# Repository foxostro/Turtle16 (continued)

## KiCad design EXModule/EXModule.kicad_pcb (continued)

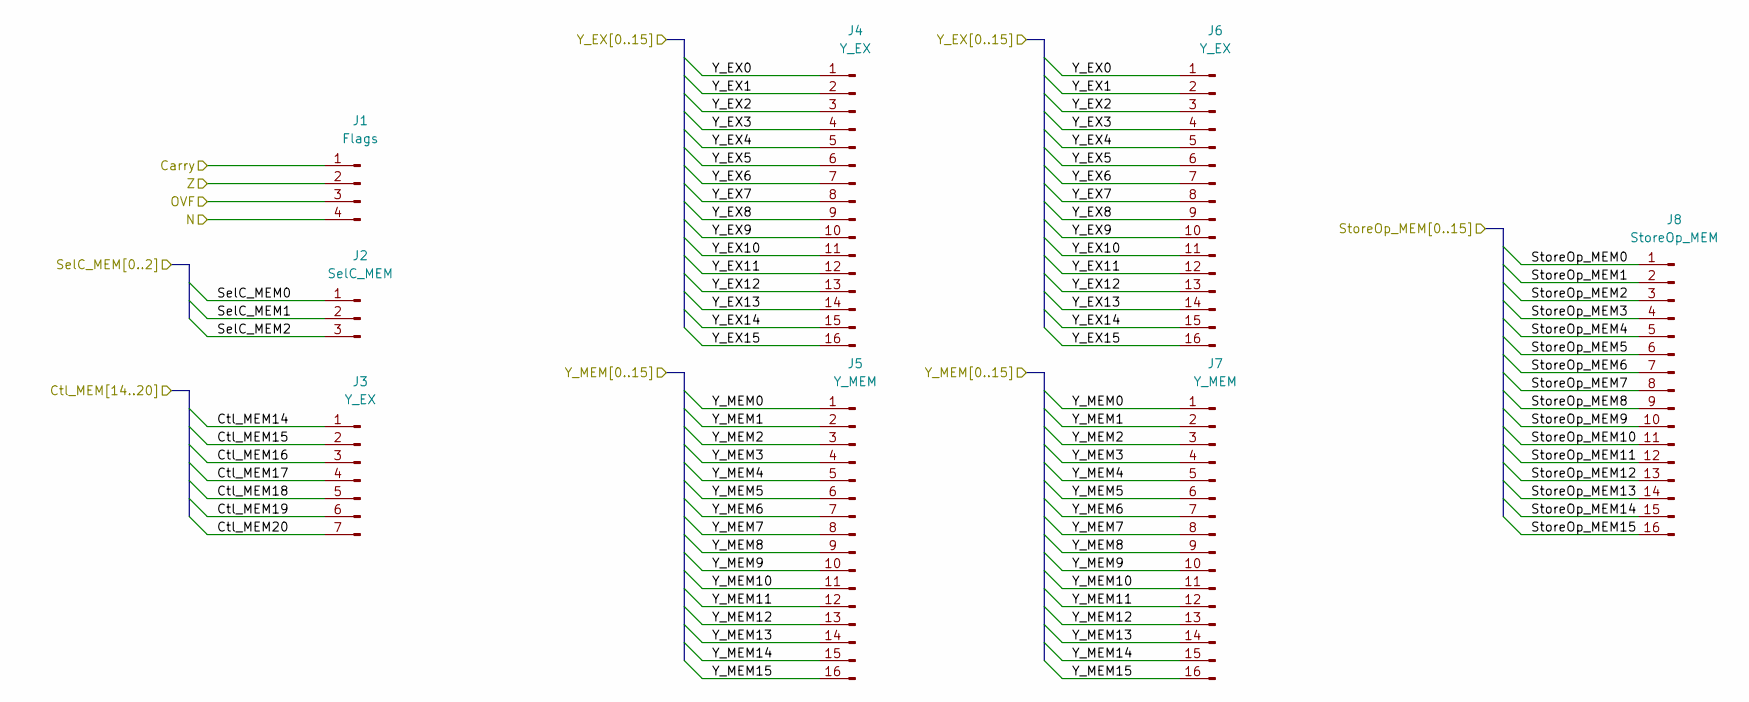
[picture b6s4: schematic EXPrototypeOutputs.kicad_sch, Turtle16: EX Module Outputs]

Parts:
J1: Flags; PinHeader_1x04_P2.54mm_Vertical
J2: SelC_MEM; PinHeader_1x03_P2.54mm_Vertical
J3: Y_EX; PinHeader_1x07_P2.54mm_Vertical
J4, J6: Y_EX; PinHeader_1x16_P2.54mm_Vertical
J5, J7: Y_MEM; PinHeader_1x16_P2.54mm_Vertical
J8: StoreOp_MEM; PinHeader_1x16_P2.54mm_Vertical

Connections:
/EX Prototype Outputs/Carry: J1.1; also elsewhere on the board
/EX Prototype Outputs/Ctl_MEM14: J3.1; also elsewhere on the board
/EX Prototype Outputs/Ctl_MEM15: J3.2; also elsewhere on the board
/EX Prototype Outputs/Ctl_MEM16: J3.3; also elsewhere on the board
/EX Prototype Outputs/Ctl_MEM17: J3.4; also elsewhere on the board
/EX Prototype Outputs/Ctl_MEM18: J3.5; also elsewhere on the board
/EX Prototype Outputs/Ctl_MEM19: J3.6; also elsewhere on the board
/EX Prototype Outputs/Ctl_MEM20: J3.7; also elsewhere on the board
/EX Prototype Outputs/N: J1.4; also elsewhere on the board
/EX Prototype Outputs/OVF: J1.3; also elsewhere on the board
/EX Prototype Outputs/SelC_MEM0: J2.1; also elsewhere on the board
/EX Prototype Outputs/SelC_MEM1: J2.2; also elsewhere on the board
/EX Prototype Outputs/SelC_MEM2: J2.3; also elsewhere on the board
/EX Prototype Outputs/StoreOp_MEM0: J8.1; also elsewhere on the board
/EX Prototype Outputs/StoreOp_MEM1: J8.2; also elsewhere on the board
/EX Prototype Outputs/StoreOp_MEM2: J8.3; also elsewhere on the board
/EX Prototype Outputs/StoreOp_MEM3: J8.4; also elsewhere on the board
/EX Prototype Outputs/StoreOp_MEM4: J8.5; also elsewhere on the board
/EX Prototype Outputs/StoreOp_MEM5: J8.6; also elsewhere on the board
/EX Prototype Outputs/StoreOp_MEM6: J8.7; also elsewhere on the board
/EX Prototype Outputs/StoreOp_MEM7: J8.8; also elsewhere on the board
/EX Prototype Outputs/StoreOp_MEM8: J8.9; also elsewhere on the board
/EX Prototype Outputs/StoreOp_MEM9: J8.10; also elsewhere on the board
/EX Prototype Outputs/StoreOp_MEM10: J8.11; also elsewhere on the board
/EX Prototype Outputs/StoreOp_MEM11: J8.12; also elsewhere on the board
/EX Prototype Outputs/StoreOp_MEM12: J8.13; also elsewhere on the board
/EX Prototype Outputs/StoreOp_MEM13: J8.14; also elsewhere on the board
/EX Prototype Outputs/StoreOp_MEM14: J8.15; also elsewhere on the board
/EX Prototype Outputs/StoreOp_MEM15: J8.16; also elsewhere on the board
/EX Prototype Outputs/Y_EX0: J4.1, J6.1; also elsewhere on the board
/EX Prototype Outputs/Y_EX1: J4.2, J6.2; also elsewhere on the board
/EX Prototype Outputs/Y_EX2: J4.3, J6.3; also elsewhere on the board
/EX Prototype Outputs/Y_EX3: J4.4, J6.4; also elsewhere on the board
/EX Prototype Outputs/Y_EX4: J4.5, J6.5; also elsewhere on the board
/EX Prototype Outputs/Y_EX5: J4.6, J6.6; also elsewhere on the board
/EX Prototype Outputs/Y_EX6: J4.7, J6.7; also elsewhere on the board
/EX Prototype Outputs/Y_EX7: J4.8, J6.8; also elsewhere on the board
/EX Prototype Outputs/Y_EX8: J4.9, J6.9; also elsewhere on the board
/EX Prototype Outputs/Y_EX9: J4.10, J6.10; also elsewhere on the board
/EX Prototype Outputs/Y_EX10: J4.11, J6.11; also elsewhere on the board
/EX Prototype Outputs/Y_EX11: J4.12, J6.12; also elsewhere on the board
/EX Prototype Outputs/Y_EX12: J4.13, J6.13; also elsewhere on the board
/EX Prototype Outputs/Y_EX13: J4.14, J6.14; also elsewhere on the board
/EX Prototype Outputs/Y_EX14: J4.15, J6.15; also elsewhere on the board
/EX Prototype Outputs/Y_EX15: J4.16, J6.16; also elsewhere on the board
/EX Prototype Outputs/Y_MEM0: J5.1, J7.1; also elsewhere on the board
/EX Prototype Outputs/Y_MEM1: J5.2, J7.2; also elsewhere on the board
/EX Prototype Outputs/Y_MEM2: J5.3, J7.3; also elsewhere on the board
/EX Prototype Outputs/Y_MEM3: J5.4, J7.4; also elsewhere on the board
/EX Prototype Outputs/Y_MEM4: J5.5, J7.5; also elsewhere on the board
/EX Prototype Outputs/Y_MEM5: J5.6, J7.6; also elsewhere on the board
/EX Prototype Outputs/Y_MEM6: J5.7, J7.7; also elsewhere on the board
/EX Prototype Outputs/Y_MEM7: J5.8, J7.8; also elsewhere on the board
/EX Prototype Outputs/Y_MEM8: J5.9, J7.9; also elsewhere on the board
/EX Prototype Outputs/Y_MEM9: J5.10, J7.10; also elsewhere on the board
/EX Prototype Outputs/Y_MEM10: J5.11, J7.11; also elsewhere on the board
/EX Prototype Outputs/Y_MEM11: J5.12, J7.12; also elsewhere on the board
/EX Prototype Outputs/Y_MEM12: J5.13, J7.13; also elsewhere on the board
/EX Prototype Outputs/Y_MEM13: J5.14, J7.14; also elsewhere on the board
/EX Prototype Outputs/Y_MEM14: J5.15, J7.15; also elsewhere on the board
/EX Prototype Outputs/Y_MEM15: J5.16, J7.16; also elsewhere on the board
/EX Prototype Outputs/Z: J1.2; also elsewhere on the board

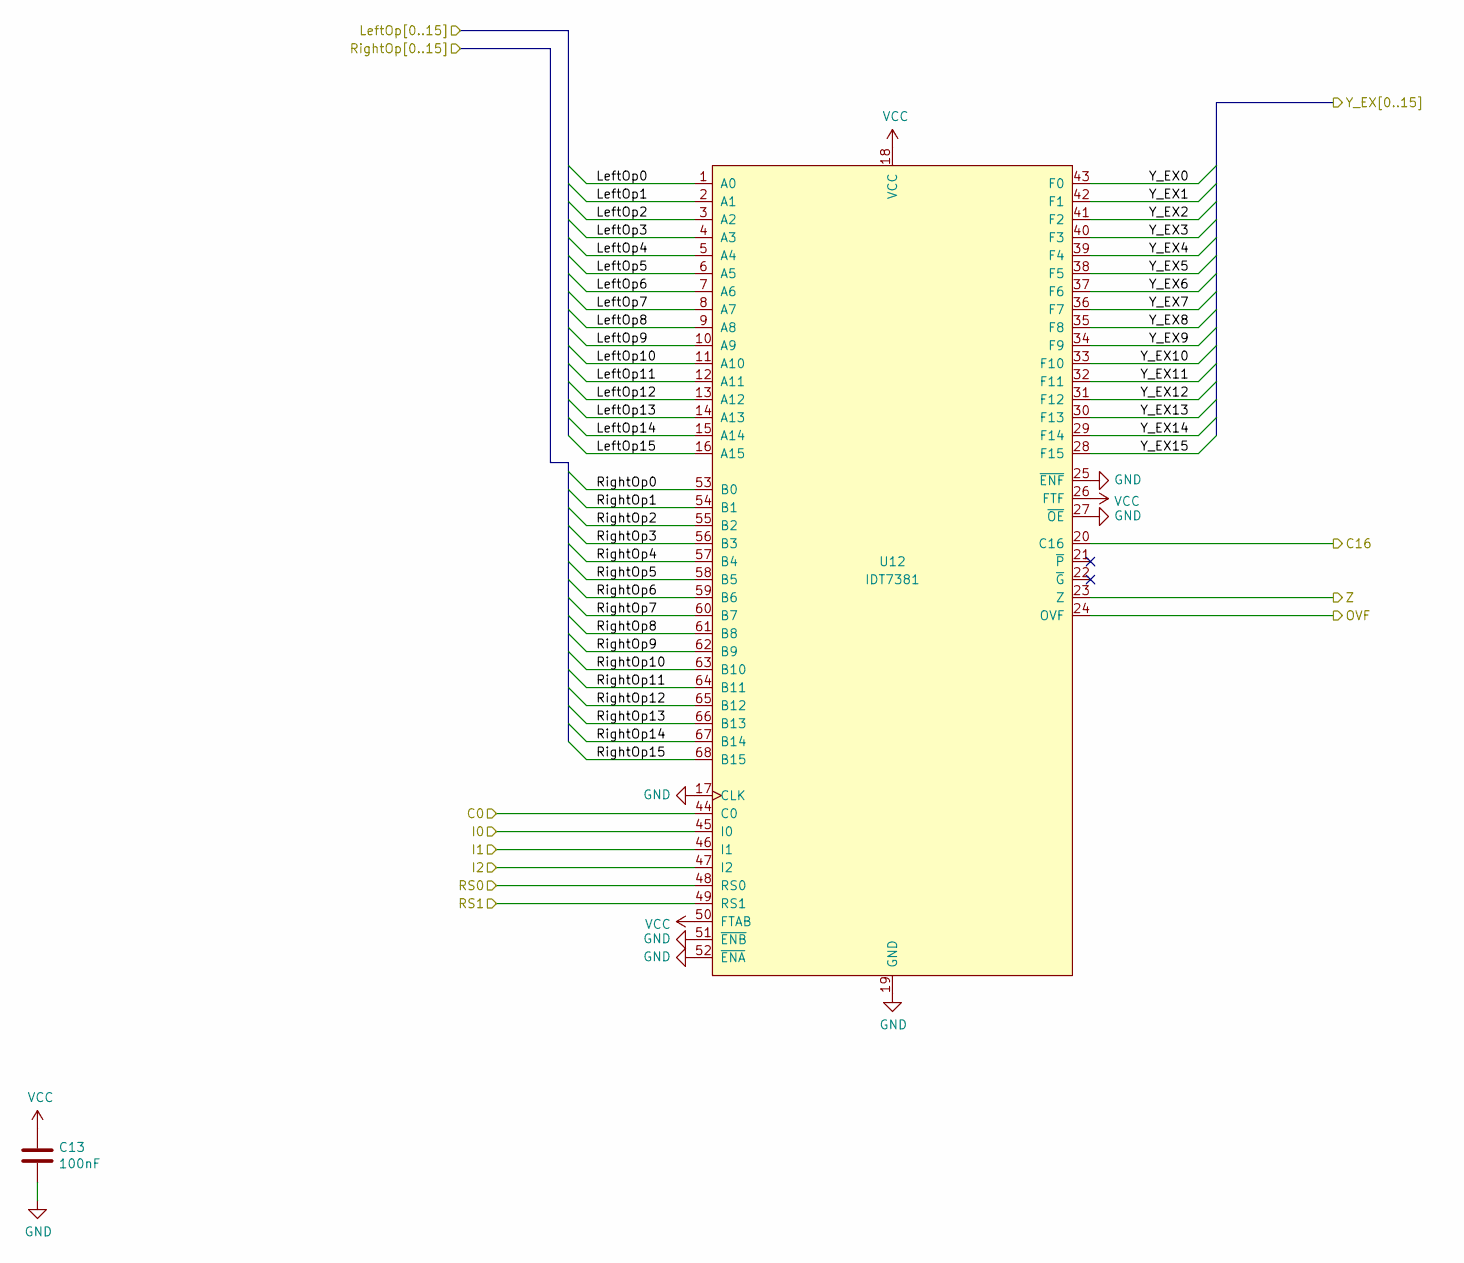
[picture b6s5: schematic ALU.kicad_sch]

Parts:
C13: 100nF; C_0603_1608Metric_Pad1.08x0.95mm_HandSolder
U12: IDT7381; PLCC-68_SMD-Socket

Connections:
/EX Prototype Inputs/A0: U12.1 (A0); also elsewhere on the board
/EX Prototype Inputs/A1: U12.2 (A1); also elsewhere on the board
/EX Prototype Inputs/A2: U12.3 (A2); also elsewhere on the board
/EX Prototype Inputs/A3: U12.4 (A3); also elsewhere on the board
/EX Prototype Inputs/A4: U12.5 (A4); also elsewhere on the board
/EX Prototype Inputs/A5: U12.6 (A5); also elsewhere on the board
/EX Prototype Inputs/A6: U12.7 (A6); also elsewhere on the board
/EX Prototype Inputs/A7: U12.8 (A7); also elsewhere on the board
/EX Prototype Inputs/A8: U12.9 (A8); also elsewhere on the board
/EX Prototype Inputs/A9: U12.10 (A9); also elsewhere on the board
/EX Prototype Inputs/A10: U12.11 (A10); also elsewhere on the board
/EX Prototype Inputs/A11: U12.12 (A11); also elsewhere on the board
/EX Prototype Inputs/A12: U12.13 (A12); also elsewhere on the board
/EX Prototype Inputs/A13: U12.14 (A13); also elsewhere on the board
/EX Prototype Inputs/A14: U12.15 (A14); also elsewhere on the board
/EX Prototype Inputs/A15: U12.16 (A15); also elsewhere on the board
/EX Prototype Inputs/Ctl_EX6: U12.44 (C0); also elsewhere on the board
/EX Prototype Inputs/Ctl_EX7: U12.45 (I0); also elsewhere on the board
/EX Prototype Inputs/Ctl_EX8: U12.46 (I1); also elsewhere on the board
/EX Prototype Inputs/Ctl_EX9: U12.47 (I2); also elsewhere on the board
/EX Prototype Inputs/Ctl_EX10: U12.48 (RS0); also elsewhere on the board
/EX Prototype Inputs/Ctl_EX11: U12.49 (RS1); also elsewhere on the board
/EX Prototype Outputs/Y_EX0: U12.43 (F0); also elsewhere on the board
/EX Prototype Outputs/Y_EX1: U12.42 (F1); also elsewhere on the board
/EX Prototype Outputs/Y_EX2: U12.41 (F2); also elsewhere on the board
/EX Prototype Outputs/Y_EX3: U12.40 (F3); also elsewhere on the board
/EX Prototype Outputs/Y_EX4: U12.39 (F4); also elsewhere on the board
/EX Prototype Outputs/Y_EX5: U12.38 (F5); also elsewhere on the board
/EX Prototype Outputs/Y_EX6: U12.37 (F6); also elsewhere on the board
/EX Prototype Outputs/Y_EX7: U12.36 (F7); also elsewhere on the board
/EX Prototype Outputs/Y_EX8: U12.35 (F8); also elsewhere on the board
/EX Prototype Outputs/Y_EX9: U12.34 (F9); also elsewhere on the board
/EX Prototype Outputs/Y_EX10: U12.33 (F10); also elsewhere on the board
/EX Prototype Outputs/Y_EX11: U12.32 (F11); also elsewhere on the board
/EX Prototype Outputs/Y_EX12: U12.31 (F12); also elsewhere on the board
/EX Prototype Outputs/Y_EX13: U12.30 (F13); also elsewhere on the board
/EX Prototype Outputs/Y_EX14: U12.29 (F14); also elsewhere on the board
/EX Prototype Outputs/Y_EX15: U12.28 (F15); also elsewhere on the board
/EX/ALU/C16: U12.20 (C16); also elsewhere on the board
/EX/ALU/OVF: U12.24 (OVF); also elsewhere on the board
/EX/ALU/RightOp0: U12.53 (B0); also elsewhere on the board
/EX/ALU/RightOp1: U12.54 (B1); also elsewhere on the board
/EX/ALU/RightOp2: U12.55 (B2); also elsewhere on the board
/EX/ALU/RightOp3: U12.56 (B3); also elsewhere on the board
/EX/ALU/RightOp4: U12.57 (B4); also elsewhere on the board
/EX/ALU/RightOp5: U12.58 (B5); also elsewhere on the board
/EX/ALU/RightOp6: U12.59 (B6); also elsewhere on the board
/EX/ALU/RightOp7: U12.60 (B7); also elsewhere on the board
/EX/ALU/RightOp8: U12.61 (B8); also elsewhere on the board
/EX/ALU/RightOp9: U12.62 (B9); also elsewhere on the board
/EX/ALU/RightOp10: U12.63 (B10); also elsewhere on the board
/EX/ALU/RightOp11: U12.64 (B11); also elsewhere on the board
/EX/ALU/RightOp12: U12.65 (B12); also elsewhere on the board
/EX/ALU/RightOp13: U12.66 (B13); also elsewhere on the board
/EX/ALU/RightOp14: U12.67 (B14); also elsewhere on the board
/EX/ALU/RightOp15: U12.68 (B15); also elsewhere on the board
/EX/ALU/Z: U12.23 (Z); also elsewhere on the board
GND: C13.2, U12.17 (CLK), U12.19 (GND), U12.25 (~ENF), U12.27 (~OE), U12.51 (~ENB), U12.52 (~ENA); also elsewhere on the board
VCC: C13.1, U12.18 (VCC), U12.26 (FTF), U12.50 (FTAB); also elsewhere on the board

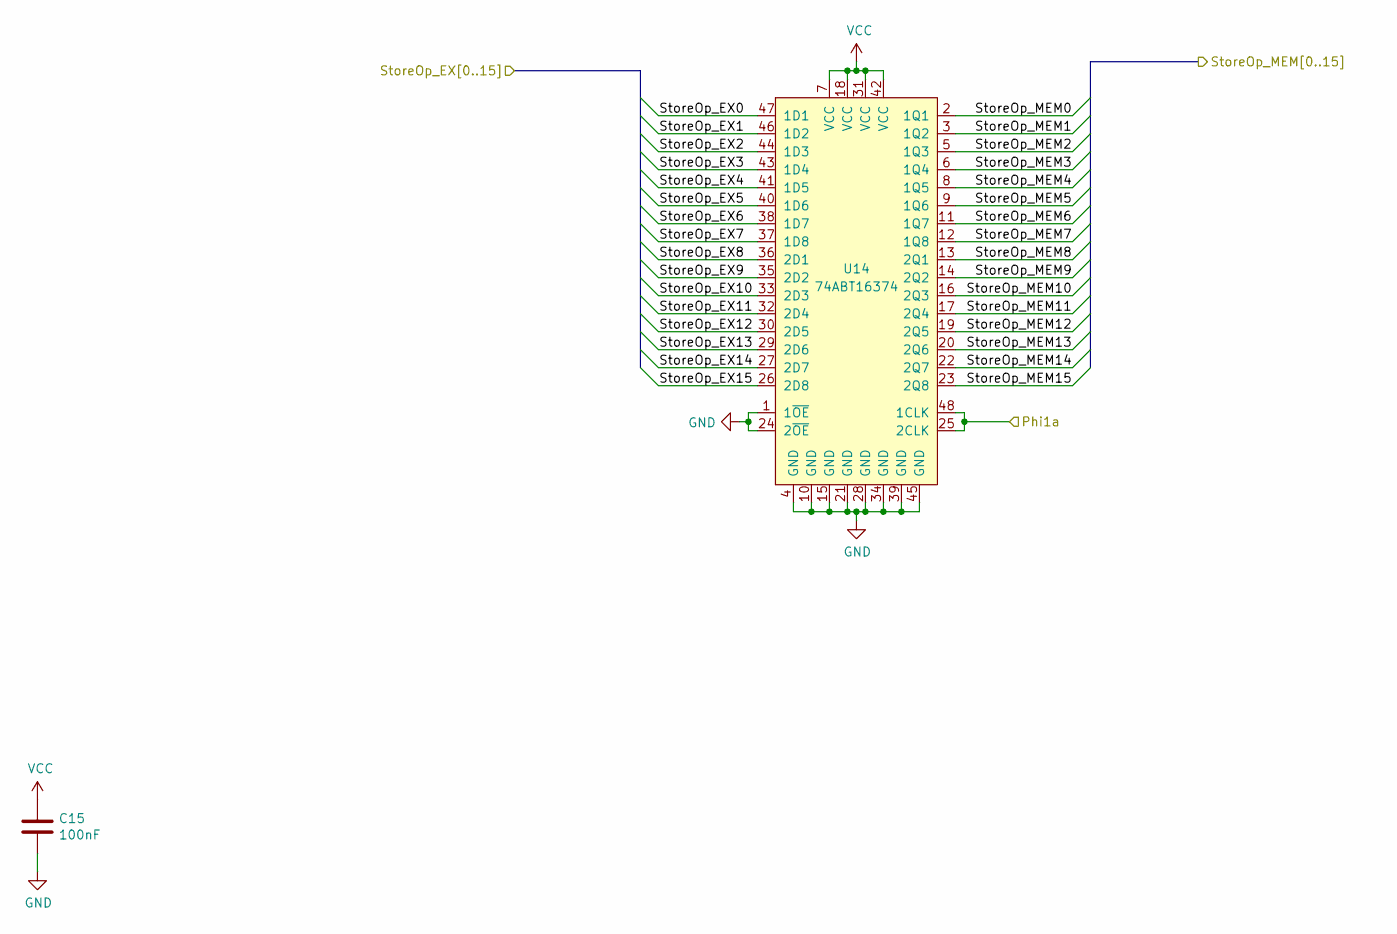
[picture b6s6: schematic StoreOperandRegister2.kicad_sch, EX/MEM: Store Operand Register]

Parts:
C15: 100nF; C_0603_1608Metric_Pad1.08x0.95mm_HandSolder
U14: 74ABT16374; TSSOP-48_6.1x12.5mm_P0.5mm

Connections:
/EX Prototype Inputs/Phi1a: U14.25 (2CLK), U14.48 (1CLK); also elsewhere on the board
/EX Prototype Outputs/StoreOp_MEM0: U14.2 (1Q1); also elsewhere on the board
/EX Prototype Outputs/StoreOp_MEM1: U14.3 (1Q2); also elsewhere on the board
/EX Prototype Outputs/StoreOp_MEM2: U14.5 (1Q3); also elsewhere on the board
/EX Prototype Outputs/StoreOp_MEM3: U14.6 (1Q4); also elsewhere on the board
/EX Prototype Outputs/StoreOp_MEM4: U14.8 (1Q5); also elsewhere on the board
/EX Prototype Outputs/StoreOp_MEM5: U14.9 (1Q6); also elsewhere on the board
/EX Prototype Outputs/StoreOp_MEM6: U14.11 (1Q7); also elsewhere on the board
/EX Prototype Outputs/StoreOp_MEM7: U14.12 (1Q8); also elsewhere on the board
/EX Prototype Outputs/StoreOp_MEM8: U14.13 (2Q1); also elsewhere on the board
/EX Prototype Outputs/StoreOp_MEM9: U14.14 (2Q2); also elsewhere on the board
/EX Prototype Outputs/StoreOp_MEM10: U14.16 (2Q3); also elsewhere on the board
/EX Prototype Outputs/StoreOp_MEM11: U14.17 (2Q4); also elsewhere on the board
/EX Prototype Outputs/StoreOp_MEM12: U14.19 (2Q5); also elsewhere on the board
/EX Prototype Outputs/StoreOp_MEM13: U14.20 (2Q6); also elsewhere on the board
/EX Prototype Outputs/StoreOp_MEM14: U14.22 (2Q7); also elsewhere on the board
/EX Prototype Outputs/StoreOp_MEM15: U14.23 (2Q8); also elsewhere on the board
/EX/sheet5FD8D6EA/StoreOp_EX0: U14.47 (1D1); also elsewhere on the board
/EX/sheet5FD8D6EA/StoreOp_EX1: U14.46 (1D2); also elsewhere on the board
/EX/sheet5FD8D6EA/StoreOp_EX2: U14.44 (1D3); also elsewhere on the board
/EX/sheet5FD8D6EA/StoreOp_EX3: U14.43 (1D4); also elsewhere on the board
/EX/sheet5FD8D6EA/StoreOp_EX4: U14.41 (1D5); also elsewhere on the board
/EX/sheet5FD8D6EA/StoreOp_EX5: U14.40 (1D6); also elsewhere on the board
/EX/sheet5FD8D6EA/StoreOp_EX6: U14.38 (1D7); also elsewhere on the board
/EX/sheet5FD8D6EA/StoreOp_EX7: U14.37 (1D8); also elsewhere on the board
/EX/sheet5FD8D6EA/StoreOp_EX8: U14.36 (2D1); also elsewhere on the board
/EX/sheet5FD8D6EA/StoreOp_EX9: U14.35 (2D2); also elsewhere on the board
/EX/sheet5FD8D6EA/StoreOp_EX10: U14.33 (2D3); also elsewhere on the board
/EX/sheet5FD8D6EA/StoreOp_EX11: U14.32 (2D4); also elsewhere on the board
/EX/sheet5FD8D6EA/StoreOp_EX12: U14.30 (2D5); also elsewhere on the board
/EX/sheet5FD8D6EA/StoreOp_EX13: U14.29 (2D6); also elsewhere on the board
/EX/sheet5FD8D6EA/StoreOp_EX14: U14.27 (2D7); also elsewhere on the board
/EX/sheet5FD8D6EA/StoreOp_EX15: U14.26 (2D8); also elsewhere on the board
GND: C15.2, U14.1 (1~OE), U14.4 (GND), U14.10 (GND), U14.15 (GND), U14.21 (GND), U14.24 (2~OE), U14.28 (GND), U14.34 (GND), U14.39 (GND), U14.45 (GND); also elsewhere on the board
VCC: C15.1, U14.7 (VCC), U14.18 (VCC), U14.31 (VCC), U14.42 (VCC); also elsewhere on the board

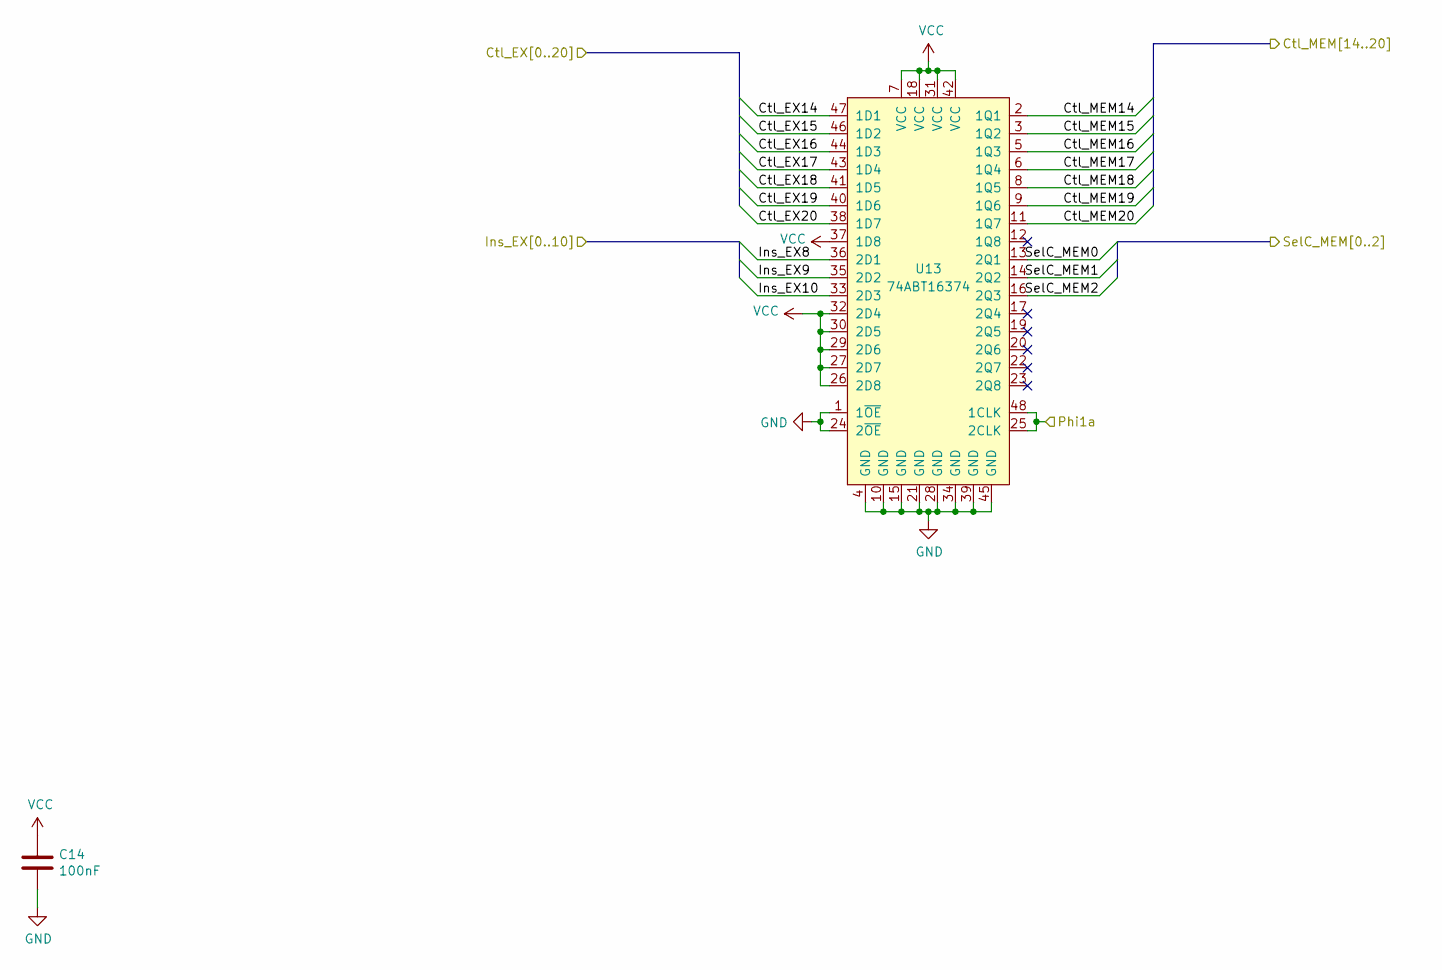
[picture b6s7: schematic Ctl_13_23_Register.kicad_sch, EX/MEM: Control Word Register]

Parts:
C14: 100nF; C_0603_1608Metric_Pad1.08x0.95mm_HandSolder
U13: 74ABT16374; TSSOP-48_6.1x12.5mm_P0.5mm

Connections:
/EX Prototype Inputs/Ctl_EX14: U13.47 (1D1); also elsewhere on the board
/EX Prototype Inputs/Ctl_EX15: U13.46 (1D2); also elsewhere on the board
/EX Prototype Inputs/Ctl_EX16: U13.44 (1D3); also elsewhere on the board
/EX Prototype Inputs/Ctl_EX17: U13.43 (1D4); also elsewhere on the board
/EX Prototype Inputs/Ctl_EX18: U13.41 (1D5); also elsewhere on the board
/EX Prototype Inputs/Ctl_EX19: U13.40 (1D6); also elsewhere on the board
/EX Prototype Inputs/Ctl_EX20: U13.38 (1D7); also elsewhere on the board
/EX Prototype Inputs/Ins_EX8: U13.36 (2D1); also elsewhere on the board
/EX Prototype Inputs/Ins_EX9: U13.35 (2D2); also elsewhere on the board
/EX Prototype Inputs/Ins_EX10: U13.33 (2D3); also elsewhere on the board
/EX Prototype Inputs/Phi1a: U13.25 (2CLK), U13.48 (1CLK); also elsewhere on the board
/EX Prototype Outputs/Ctl_MEM14: U13.2 (1Q1); also elsewhere on the board
/EX Prototype Outputs/Ctl_MEM15: U13.3 (1Q2); also elsewhere on the board
/EX Prototype Outputs/Ctl_MEM16: U13.5 (1Q3); also elsewhere on the board
/EX Prototype Outputs/Ctl_MEM17: U13.6 (1Q4); also elsewhere on the board
/EX Prototype Outputs/Ctl_MEM18: U13.8 (1Q5); also elsewhere on the board
/EX Prototype Outputs/Ctl_MEM19: U13.9 (1Q6); also elsewhere on the board
/EX Prototype Outputs/Ctl_MEM20: U13.11 (1Q7); also elsewhere on the board
/EX Prototype Outputs/SelC_MEM0: U13.13 (2Q1); also elsewhere on the board
/EX Prototype Outputs/SelC_MEM1: U13.14 (2Q2); also elsewhere on the board
/EX Prototype Outputs/SelC_MEM2: U13.16 (2Q3); also elsewhere on the board
GND: C14.2, U13.1 (1~OE), U13.4 (GND), U13.10 (GND), U13.15 (GND), U13.21 (GND), U13.24 (2~OE), U13.28 (GND), U13.34 (GND), U13.39 (GND), U13.45 (GND); also elsewhere on the board
VCC: C14.1, U13.7 (VCC), U13.18 (VCC), U13.26 (2D8), U13.27 (2D7), U13.29 (2D6), U13.30 (2D5), U13.31 (VCC), U13.32 (2D4), U13.37 (1D8), U13.42 (VCC); also elsewhere on the board

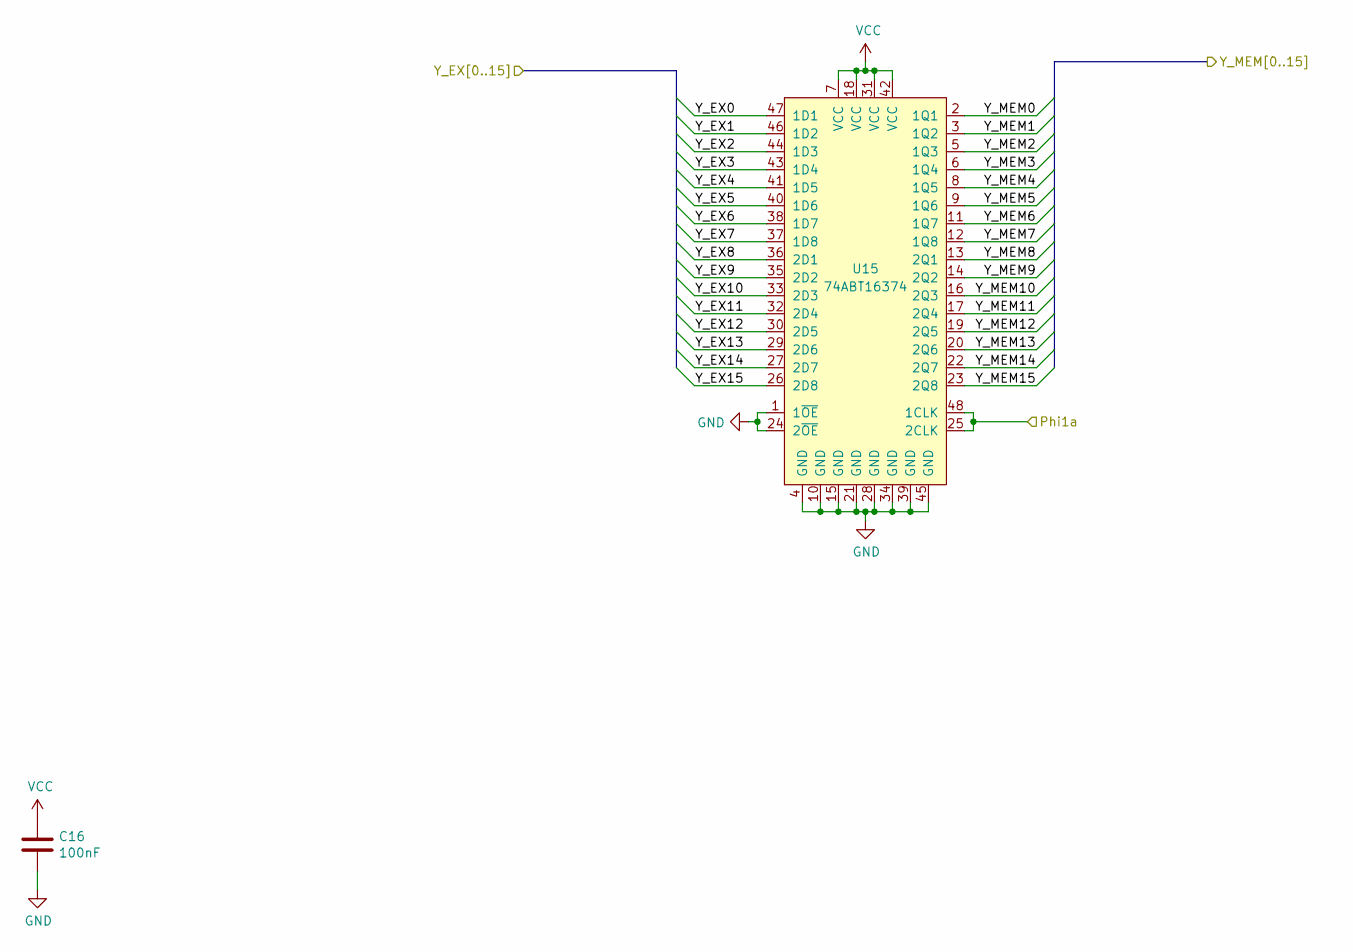
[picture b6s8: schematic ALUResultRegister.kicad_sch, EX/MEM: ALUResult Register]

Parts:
C16: 100nF; C_0603_1608Metric_Pad1.08x0.95mm_HandSolder
U15: 74ABT16374; TSSOP-48_6.1x12.5mm_P0.5mm

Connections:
/EX Prototype Inputs/Phi1a: U15.25 (2CLK), U15.48 (1CLK); also elsewhere on the board
/EX Prototype Outputs/Y_EX0: U15.47 (1D1); also elsewhere on the board
/EX Prototype Outputs/Y_EX1: U15.46 (1D2); also elsewhere on the board
/EX Prototype Outputs/Y_EX2: U15.44 (1D3); also elsewhere on the board
/EX Prototype Outputs/Y_EX3: U15.43 (1D4); also elsewhere on the board
/EX Prototype Outputs/Y_EX4: U15.41 (1D5); also elsewhere on the board
/EX Prototype Outputs/Y_EX5: U15.40 (1D6); also elsewhere on the board
/EX Prototype Outputs/Y_EX6: U15.38 (1D7); also elsewhere on the board
/EX Prototype Outputs/Y_EX7: U15.37 (1D8); also elsewhere on the board
/EX Prototype Outputs/Y_EX8: U15.36 (2D1); also elsewhere on the board
/EX Prototype Outputs/Y_EX9: U15.35 (2D2); also elsewhere on the board
/EX Prototype Outputs/Y_EX10: U15.33 (2D3); also elsewhere on the board
/EX Prototype Outputs/Y_EX11: U15.32 (2D4); also elsewhere on the board
/EX Prototype Outputs/Y_EX12: U15.30 (2D5); also elsewhere on the board
/EX Prototype Outputs/Y_EX13: U15.29 (2D6); also elsewhere on the board
/EX Prototype Outputs/Y_EX14: U15.27 (2D7); also elsewhere on the board
/EX Prototype Outputs/Y_EX15: U15.26 (2D8); also elsewhere on the board
/EX Prototype Outputs/Y_MEM0: U15.2 (1Q1); also elsewhere on the board
/EX Prototype Outputs/Y_MEM1: U15.3 (1Q2); also elsewhere on the board
/EX Prototype Outputs/Y_MEM2: U15.5 (1Q3); also elsewhere on the board
/EX Prototype Outputs/Y_MEM3: U15.6 (1Q4); also elsewhere on the board
/EX Prototype Outputs/Y_MEM4: U15.8 (1Q5); also elsewhere on the board
/EX Prototype Outputs/Y_MEM5: U15.9 (1Q6); also elsewhere on the board
/EX Prototype Outputs/Y_MEM6: U15.11 (1Q7); also elsewhere on the board
/EX Prototype Outputs/Y_MEM7: U15.12 (1Q8); also elsewhere on the board
/EX Prototype Outputs/Y_MEM8: U15.13 (2Q1); also elsewhere on the board
/EX Prototype Outputs/Y_MEM9: U15.14 (2Q2); also elsewhere on the board
/EX Prototype Outputs/Y_MEM10: U15.16 (2Q3); also elsewhere on the board
/EX Prototype Outputs/Y_MEM11: U15.17 (2Q4); also elsewhere on the board
/EX Prototype Outputs/Y_MEM12: U15.19 (2Q5); also elsewhere on the board
/EX Prototype Outputs/Y_MEM13: U15.20 (2Q6); also elsewhere on the board
/EX Prototype Outputs/Y_MEM14: U15.22 (2Q7); also elsewhere on the board
/EX Prototype Outputs/Y_MEM15: U15.23 (2Q8); also elsewhere on the board
GND: C16.2, U15.1 (1~OE), U15.4 (GND), U15.10 (GND), U15.15 (GND), U15.21 (GND), U15.24 (2~OE), U15.28 (GND), U15.34 (GND), U15.39 (GND), U15.45 (GND); also elsewhere on the board
VCC: C16.1, U15.7 (VCC), U15.18 (VCC), U15.31 (VCC), U15.42 (VCC); also elsewhere on the board

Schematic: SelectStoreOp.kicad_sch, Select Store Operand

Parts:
C8, C9, C10, C11, C12: 100nF; C_0603_1608Metric_Pad1.08x0.95mm_HandSolder
U7, U9, U10, U11: 74AHCT16245; TSSOP-48_6.1x12.5mm_P0.5mm
U8: 74AHCT138; TSSOP-16_4.4x5mm_P0.65mm

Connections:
/EX Prototype Inputs/B0: U7.47 (1A1); also elsewhere on the board
/EX Prototype Inputs/B1: U7.46 (1A2); also elsewhere on the board
/EX Prototype Inputs/B2: U7.44 (1A3); also elsewhere on the board
/EX Prototype Inputs/B3: U7.43 (1A4); also elsewhere on the board
/EX Prototype Inputs/B4: U7.41 (1A5); also elsewhere on the board
/EX Prototype Inputs/B5: U7.40 (1A6); also elsewhere on the board
/EX Prototype Inputs/B6: U7.38 (1A7); also elsewhere on the board
/EX Prototype Inputs/B7: U7.37 (1A8); also elsewhere on the board
/EX Prototype Inputs/B8: U7.36 (2A1); also elsewhere on the board
/EX Prototype Inputs/B9: U7.35 (2A2); also elsewhere on the board
/EX Prototype Inputs/B10: U7.33 (2A3); also elsewhere on the board
/EX Prototype Inputs/B11: U7.32 (2A4); also elsewhere on the board
/EX Prototype Inputs/B12: U7.30 (2A5); also elsewhere on the board
/EX Prototype Inputs/B13: U7.29 (2A6); also elsewhere on the board
/EX Prototype Inputs/B14: U7.27 (2A7); also elsewhere on the board
/EX Prototype Inputs/B15: U7.26 (2A8); also elsewhere on the board
/EX Prototype Inputs/Ctl_EX1: U8.1 (A0); also elsewhere on the board
/EX Prototype Inputs/Ctl_EX2: U8.2 (A1); also elsewhere on the board
/EX Prototype Inputs/Ins_EX0: U10.47 (1A1), U11.36 (2A1); also elsewhere on the board
/EX Prototype Inputs/Ins_EX1: U10.46 (1A2), U11.35 (2A2); also elsewhere on the board
/EX Prototype Inputs/Ins_EX2: U10.44 (1A3), U11.33 (2A3); also elsewhere on the board
/EX Prototype Inputs/Ins_EX3: U10.43 (1A4), U11.32 (2A4); also elsewhere on the board
/EX Prototype Inputs/Ins_EX4: U10.41 (1A5), U11.30 (2A5); also elsewhere on the board
/EX Prototype Inputs/Ins_EX5: U10.40 (1A6), U11.29 (2A6); also elsewhere on the board
/EX Prototype Inputs/Ins_EX6: U10.38 (1A7), U11.27 (2A7); also elsewhere on the board
/EX Prototype Inputs/Ins_EX7: U10.26 (2A8), U10.27 (2A7), U10.29 (2A6), U10.30 (2A5), U10.32 (2A4), U10.33 (2A3), U10.35 (2A2), U10.36 (2A1), U10.37 (1A8), U11.26 (2A8); also elsewhere on the board
/EX Prototype Inputs/PC_EX0: U9.47 (1A1); also elsewhere on the board
/EX Prototype Inputs/PC_EX1: U9.46 (1A2); also elsewhere on the board
/EX Prototype Inputs/PC_EX2: U9.44 (1A3); also elsewhere on the board
/EX Prototype Inputs/PC_EX3: U9.43 (1A4); also elsewhere on the board
/EX Prototype Inputs/PC_EX4: U9.41 (1A5); also elsewhere on the board
/EX Prototype Inputs/PC_EX5: U9.40 (1A6); also elsewhere on the board
/EX Prototype Inputs/PC_EX6: U9.38 (1A7); also elsewhere on the board
/EX Prototype Inputs/PC_EX7: U9.37 (1A8); also elsewhere on the board
/EX Prototype Inputs/PC_EX8: U9.36 (2A1); also elsewhere on the board
/EX Prototype Inputs/PC_EX9: U9.35 (2A2); also elsewhere on the board
/EX Prototype Inputs/PC_EX10: U9.33 (2A3); also elsewhere on the board
/EX Prototype Inputs/PC_EX11: U9.32 (2A4); also elsewhere on the board
/EX Prototype Inputs/PC_EX12: U9.30 (2A5); also elsewhere on the board
/EX Prototype Inputs/PC_EX13: U9.29 (2A6); also elsewhere on the board
/EX Prototype Inputs/PC_EX14: U9.27 (2A7); also elsewhere on the board
/EX Prototype Inputs/PC_EX15: U9.26 (2A8); also elsewhere on the board
/EX/sheet5FD8D6EA/StoreOp_EX0: U7.2 (1B1), U9.2 (1B1), U10.2 (1B1), U11.2 (1B1); also elsewhere on the board
/EX/sheet5FD8D6EA/StoreOp_EX1: U7.3 (1B2), U9.3 (1B2), U10.3 (1B2), U11.3 (1B2); also elsewhere on the board
/EX/sheet5FD8D6EA/StoreOp_EX2: U7.5 (1B3), U9.5 (1B3), U10.5 (1B3), U11.5 (1B3); also elsewhere on the board
/EX/sheet5FD8D6EA/StoreOp_EX3: U7.6 (1B4), U9.6 (1B4), U10.6 (1B4), U11.6 (1B4); also elsewhere on the board
/EX/sheet5FD8D6EA/StoreOp_EX4: U7.8 (1B5), U9.8 (1B5), U10.8 (1B5), U11.8 (1B5); also elsewhere on the board
/EX/sheet5FD8D6EA/StoreOp_EX5: U7.9 (1B6), U9.9 (1B6), U10.9 (1B6), U11.9 (1B6); also elsewhere on the board
/EX/sheet5FD8D6EA/StoreOp_EX6: U7.11 (1B7), U9.11 (1B7), U10.11 (1B7), U11.11 (1B7); also elsewhere on the board
/EX/sheet5FD8D6EA/StoreOp_EX7: U7.12 (1B8), U9.12 (1B8), U10.12 (1B8), U11.12 (1B8); also elsewhere on the board
/EX/sheet5FD8D6EA/StoreOp_EX8: U7.13 (2B1), U9.13 (2B1), U10.13 (2B1), U11.13 (2B1); also elsewhere on the board
/EX/sheet5FD8D6EA/StoreOp_EX9: U7.14 (2B2), U9.14 (2B2), U10.14 (2B2), U11.14 (2B2); also elsewhere on the board
/EX/sheet5FD8D6EA/StoreOp_EX10: U7.16 (2B3), U9.16 (2B3), U10.16 (2B3), U11.16 (2B3); also elsewhere on the board
/EX/sheet5FD8D6EA/StoreOp_EX11: U7.17 (2B4), U9.17 (2B4), U10.17 (2B4), U11.17 (2B4); also elsewhere on the board
/EX/sheet5FD8D6EA/StoreOp_EX12: U7.19 (2B5), U9.19 (2B5), U10.19 (2B5), U11.19 (2B5); also elsewhere on the board
/EX/sheet5FD8D6EA/StoreOp_EX13: U7.20 (2B6), U9.20 (2B6), U10.20 (2B6), U11.20 (2B6); also elsewhere on the board
/EX/sheet5FD8D6EA/StoreOp_EX14: U7.22 (2B7), U9.22 (2B7), U10.22 (2B7), U11.22 (2B7); also elsewhere on the board
/EX/sheet5FD8D6EA/StoreOp_EX15: U7.23 (2B8), U9.23 (2B8), U10.23 (2B8), U11.23 (2B8); also elsewhere on the board
GND: C8.2, C9.2, C10.2, C11.2, C12.2, U7.4 (GND), U7.10 (GND), U7.15 (GND), U7.21 (GND), U7.28 (GND), U7.34 (GND), U7.39 (GND), U7.45 (GND), U8.3 (A2), U8.4 (E1), U8.5 (E2), U8.8 (GND), U9.4 (GND), U9.10 (GND), U9.15 (GND), U9.21 (GND), U9.28 (GND), U9.34 (GND), U9.39 (GND), U9.45 (GND), U10.4 (GND), U10.10 (GND), U10.15 (GND), U10.21 (GND), U10.28 (GND), U10.34 (GND), U10.39 (GND), U10.45 (GND), U11.4 (GND), U11.10 (GND), U11.15 (GND), U11.21 (GND), U11.28 (GND), U11.34 (GND), U11.37 (1A8), U11.38 (1A7), U11.39 (GND), U11.40 (1A6), U11.41 (1A5), U11.43 (1A4), U11.44 (1A3), U11.45 (GND), U11.46 (1A2), U11.47 (1A1); also elsewhere on the board
unnamed: U7.25 (2~OE), U7.48 (1~OE), U8.15 (O0)
unnamed: U8.14 (O1), U9.25 (2~OE), U9.48 (1~OE)
unnamed: U8.13 (O2), U10.25 (2~OE), U10.48 (1~OE)
unnamed: U8.12 (O3), U11.25 (2~OE), U11.48 (1~OE)
VCC: C8.1, C9.1, C10.1, C11.1, C12.1, U7.1 (1DIR), U7.7 (VCC), U7.18 (VCC), U7.24 (2DIR), U7.31 (VCC), U7.42 (VCC), U8.6 (E3), U8.16 (VCC), U9.1 (1DIR), U9.7 (VCC), U9.18 (VCC), U9.24 (2DIR), U9.31 (VCC), U9.42 (VCC), U10.1 (1DIR), U10.7 (VCC), U10.18 (VCC), U10.24 (2DIR), U10.31 (VCC), U10.42 (VCC), U11.1 (1DIR), U11.7 (VCC), U11.18 (VCC), U11.24 (2DIR), U11.31 (VCC), U11.42 (VCC); also elsewhere on the board

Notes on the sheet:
SelStoreOp=0 —> Select Register B SelStoreOp=1 —> Select PC+1 (return address) SelStoreOp=2 —> Select 8-bit Immediate Value SelStoreOp=3 —> Select 8-bit Immediate Value << 8
